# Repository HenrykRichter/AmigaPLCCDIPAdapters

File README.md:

# AmigaPLCCDIPAdapters
PLCC to DIP Adapters for Amiga Computers

The main part of this project are adapter PCB designs for Commodore PLCC chips to be used in conjunction
with DIP sockets in Amiga 500/2000/3000 computers. Since parts availability of those chips has dwindled in
recent years, the PLCC variants of CSG8373R4PL, CSG8364R7PL and CSG8520PL have become more interesting as
parts replacements.

Another sub-project in here is a replacement for the Video DAC (or Video Hybrid, CSG part number 390229-0x).
While other OpenSource designs exist for the Video Hybrid (e.g. from [Sukko Pera](https://github.com/SukkoPera/OpenAmigaVideoHybrid)), this
alternative design is based on 0603 parts and much smaller than other designs I am aware of. 
The Video Hybrid may be used in A500(+), A1000, A2000, A3000 and on Commodore's A2320 DeInterlacer. Like the
original, it supports 12 Bit RGB and monochrome composite outputs.

## Building Notes

I would suggest to solder the pin strips first. Once done, the best course of action is to shorten the
pins who sit under the PLCC socket. Mount the PLCC socket next and carefully solder its pins at the underside of the board.

## Parts list for Denise and Paula Adapters
- PCB
- 2 pin strips 2.54mm, 24 pins each (e.g. BKL 10120538 at Reichelt.de)
- 1 THT PLCC socket, 52 pins (e.g. 575-945224 at Mouser or PLCC 52 at Reichelt.de)

## Parts list for CIA Adapters
- PCB
- 2 pin strips 2.54mm, 20 pins each (e.g. BKL 10120536 at Reichelt.de)
- 1 THT PLCC socket, 44 pins (e.g. PLCC 44 at Reichelt.de)
- 1 pin strip angled 1x4 RM2.54 (e.g. W+P 946-134 at Reichelt.de), optional
Please note that the angled 1x4 connector is useful only if you are going to extract
the DTR or CTS signals for further use (CIA-B only). Otherwise, it doesn't need to
be fitted.

## Video Hybrid

The unfortunate side effect of a small board size is the lack of space for a nice silkscreen. Depending
on the available print resolution of the PCB manufacturer, the parts indicators might not be quite easily
visible. Consequently, I've put a picture into the Pics/ subfolder where the proper part locations are
identified.

## Pictures

## License
The PCB, it's design files and all support code are licensed as [CC BY NC SA](https://creativecommons.org/licenses/by-nc-sa/4.0/deed.en).

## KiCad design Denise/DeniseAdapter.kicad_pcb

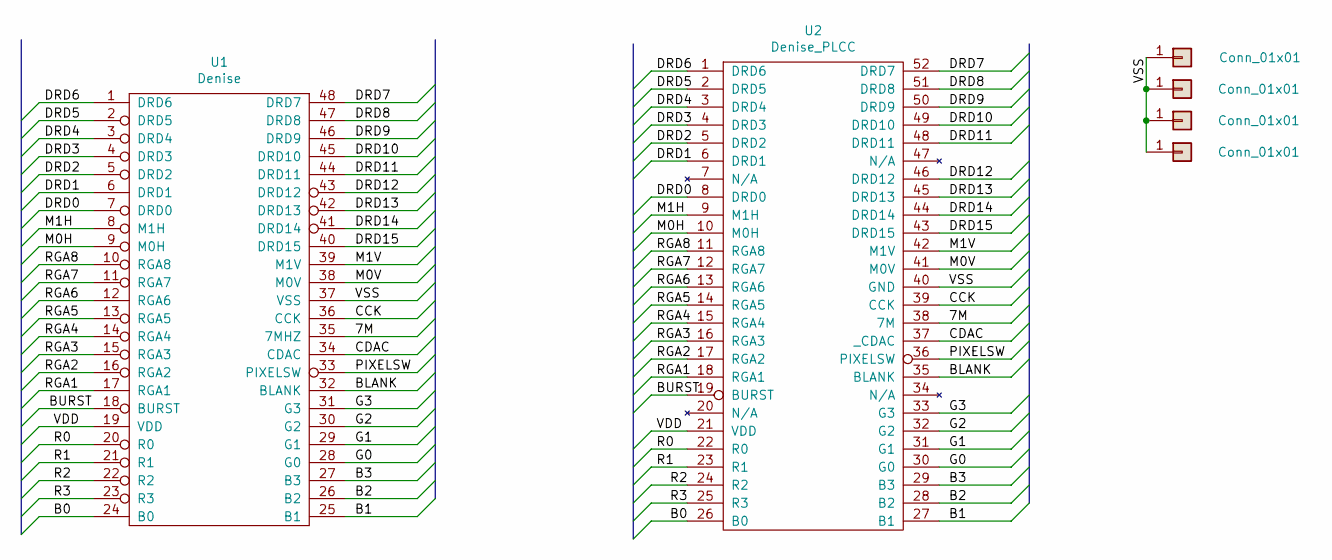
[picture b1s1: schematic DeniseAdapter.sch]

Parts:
J1, J2, J3, J4: Conn_01x01; MountingHole_3mm
U1: Denise; DIP-48_W15.24mm_Socket
U2: Denise_PLCC; PLCC-52_THT-Socket

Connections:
/7M: U1.35 (7MHZ), U2.38 (7M)
/B0: U1.24 (B0), U2.26 (B0)
/B1: U1.25 (B1), U2.27 (B1)
/B2: U1.26 (B2), U2.28 (B2)
/B3: U1.27 (B3), U2.29 (B3)
/BLANK: U1.32 (BLANK), U2.35 (BLANK)
/BURST: U1.18 (BURST), U2.19 (BURST)
/CCK: U1.36 (CCK), U2.39 (CCK)
/CDAC: U1.34 (CDAC), U2.37 (_CDAC)
/DRD0: U1.7 (DRD0), U2.8 (DRD0)
/DRD1: U1.6 (DRD1), U2.6 (DRD1)
/DRD2: U1.5 (DRD2), U2.5 (DRD2)
/DRD3: U1.4 (DRD3), U2.4 (DRD3)
/DRD4: U1.3 (DRD4), U2.3 (DRD4)
/DRD5: U1.2 (DRD5), U2.2 (DRD5)
/DRD6: U1.1 (DRD6), U2.1 (DRD6)
/DRD7: U1.48 (DRD7), U2.52 (DRD7)
/DRD8: U1.47 (DRD8), U2.51 (DRD8)
/DRD9: U1.46 (DRD9), U2.50 (DRD9)
/DRD10: U1.45 (DRD10), U2.49 (DRD10)
/DRD11: U1.44 (DRD11), U2.48 (DRD11)
/DRD12: U1.43 (DRD12), U2.46 (DRD12)
/DRD13: U1.42 (DRD13), U2.45 (DRD13)
/DRD14: U1.41 (DRD14), U2.44 (DRD14)
/DRD15: U1.40 (DRD15), U2.43 (DRD15)
/G0: U1.28 (G0), U2.30 (G0)
/G1: U1.29 (G1), U2.31 (G1)
/G2: U1.30 (G2), U2.32 (G2)
/G3: U1.31 (G3), U2.33 (G3)
/M0H: U1.9 (M0H), U2.10 (M0H)
/M0V: U1.38 (M0V), U2.41 (M0V)
/M1H: U1.8 (M1H), U2.9 (M1H)
/M1V: U1.39 (M1V), U2.42 (M1V)
/PIXELSW: U1.33 (PIXELSW), U2.36 (PIXELSW)
/R0: U1.20 (R0), U2.22 (R0)
/R1: U1.21 (R1), U2.23 (R1)
/R2: U1.22 (R2), U2.24 (R2)
/R3: U1.23 (R3), U2.25 (R3)
/RGA1: U1.17 (RGA1), U2.18 (RGA1)
/RGA2: U1.16 (RGA2), U2.17 (RGA2)
/RGA3: U1.15 (RGA3), U2.16 (RGA3)
/RGA4: U1.14 (RGA4), U2.15 (RGA4)
/RGA5: U1.13 (RGA5), U2.14 (RGA5)
/RGA6: U1.12 (RGA6), U2.13 (RGA6)
/RGA7: U1.11 (RGA7), U2.12 (RGA7)
/RGA8: U1.10 (RGA8), U2.11 (RGA8)
/VDD: U1.19 (VDD), U2.21 (VDD)
/VSS: J1.1, J2.1, J3.1, J4.1, U1.37 (VSS), U2.40 (GND)

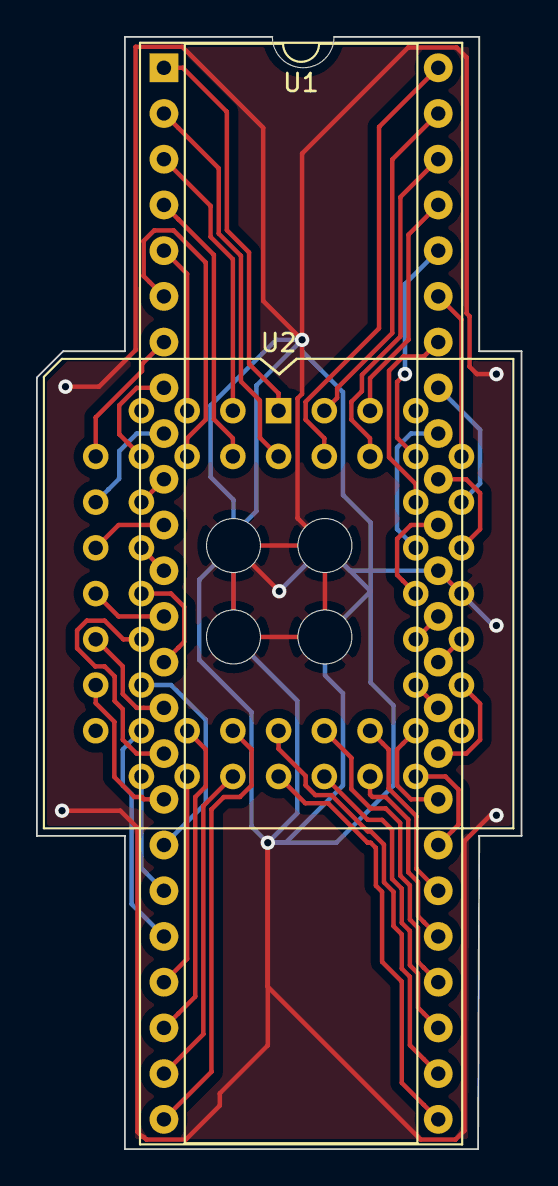
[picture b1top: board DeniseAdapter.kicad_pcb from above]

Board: 2 copper layers, 26.9 x 61.8 mm, 6 parts (0 on the bottom side), 48 nets.

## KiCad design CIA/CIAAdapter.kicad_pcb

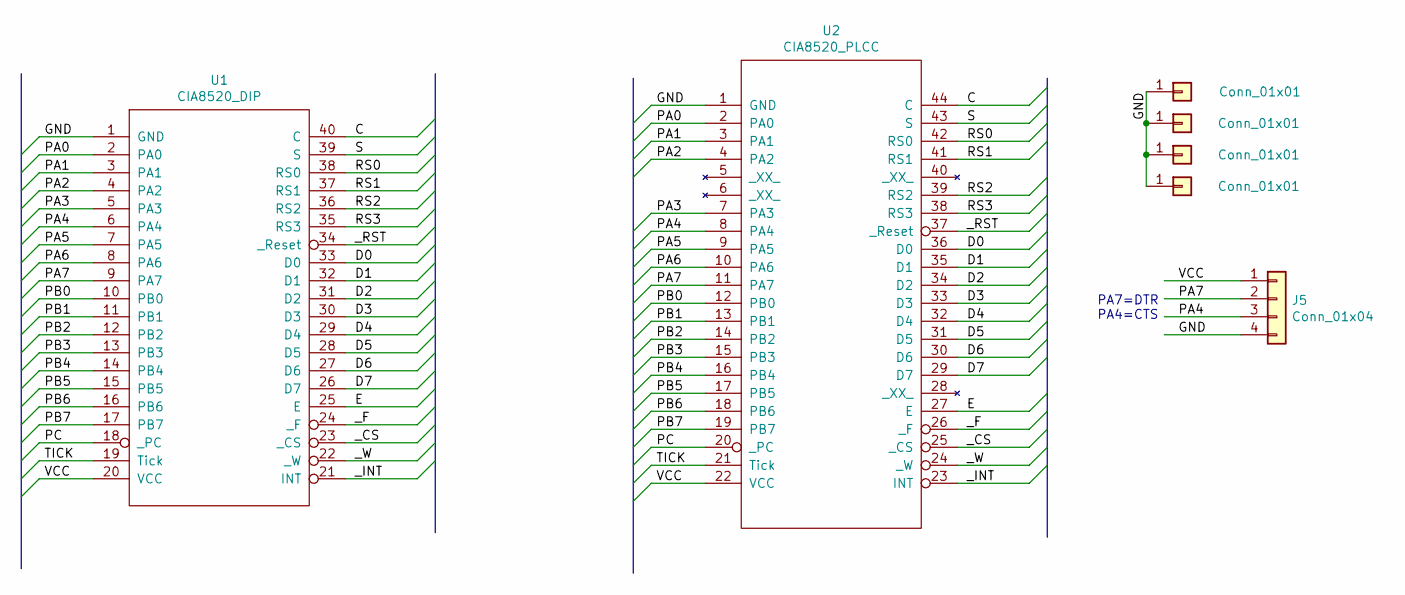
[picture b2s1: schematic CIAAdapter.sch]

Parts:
J1, J2, J3, J4: Conn_01x01; MountingHole_3mm
J5: Conn_01x04; PinHeader_1x04_P2.54mm_Vertical
U1: CIA8520_DIP; DIP-40_W15.24mm
U2: CIA8520_PLCC; PLCC-44_THT-Socket

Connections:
/C: U1.40 (C), U2.44 (C)
/D0: U1.33 (D0), U2.36 (D0)
/D1: U1.32 (D1), U2.35 (D1)
/D2: U1.31 (D2), U2.34 (D2)
/D3: U1.30 (D3), U2.33 (D3)
/D4: U1.29 (D4), U2.32 (D4)
/D5: U1.28 (D5), U2.31 (D5)
/D6: U1.27 (D6), U2.30 (D6)
/D7: U1.26 (D7), U2.29 (D7)
/E: U1.25 (E), U2.27 (E)
/GND: J1.1, J2.1, J3.1, J4.1, J5.4, U1.1 (GND), U2.1 (GND)
/PA0: U1.2 (PA0), U2.2 (PA0)
/PA1: U1.3 (PA1), U2.3 (PA1)
/PA2: U1.4 (PA2), U2.4 (PA2)
/PA3: U1.5 (PA3), U2.7 (PA3)
/PA4: J5.3, U1.6 (PA4), U2.8 (PA4)
/PA5: U1.7 (PA5), U2.9 (PA5)
/PA6: U1.8 (PA6), U2.10 (PA6)
/PA7: J5.2, U1.9 (PA7), U2.11 (PA7)
/PB0: U1.10 (PB0), U2.12 (PB0)
/PB1: U1.11 (PB1), U2.13 (PB1)
/PB2: U1.12 (PB2), U2.14 (PB2)
/PB3: U1.13 (PB3), U2.15 (PB3)
/PB4: U1.14 (PB4), U2.16 (PB4)
/PB5: U1.15 (PB5), U2.17 (PB5)
/PB6: U1.16 (PB6), U2.18 (PB6)
/PB7: U1.17 (PB7), U2.19 (PB7)
/PC: U1.18 (_PC), U2.20 (_PC)
/RS0: U1.38 (RS0), U2.42 (RS0)
/RS1: U1.37 (RS1), U2.41 (RS1)
/RS2: U1.36 (RS2), U2.39 (RS2)
/RS3: U1.35 (RS3), U2.38 (RS3)
/S: U1.39 (S), U2.43 (S)
/TICK: U1.19 (Tick), U2.21 (Tick)
/VCC: J5.1, U1.20 (VCC), U2.22 (VCC)
/_CS: U1.23 (_CS), U2.25 (_CS)
/_F: U1.24 (_F), U2.26 (_F)
/_INT: U1.21 (INT), U2.23 (INT)
/_RST: U1.34 (_Reset), U2.37 (_Reset)
/_W: U1.22 (_W), U2.24 (_W)

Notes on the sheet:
PA7=DTR PA4=CTS

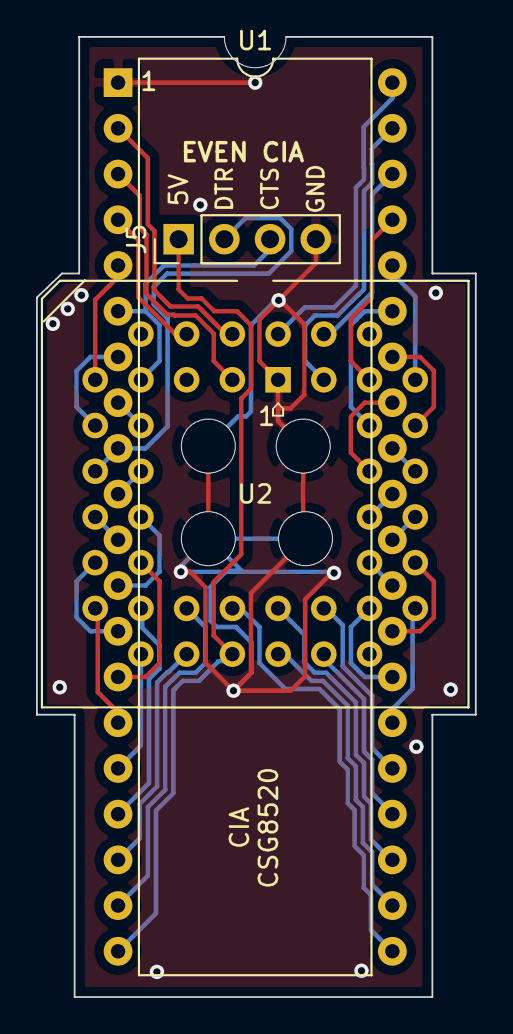
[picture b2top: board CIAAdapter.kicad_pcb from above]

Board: 2 copper layers, 24.4 x 53.3 mm, 7 parts (0 on the bottom side), 40 nets.

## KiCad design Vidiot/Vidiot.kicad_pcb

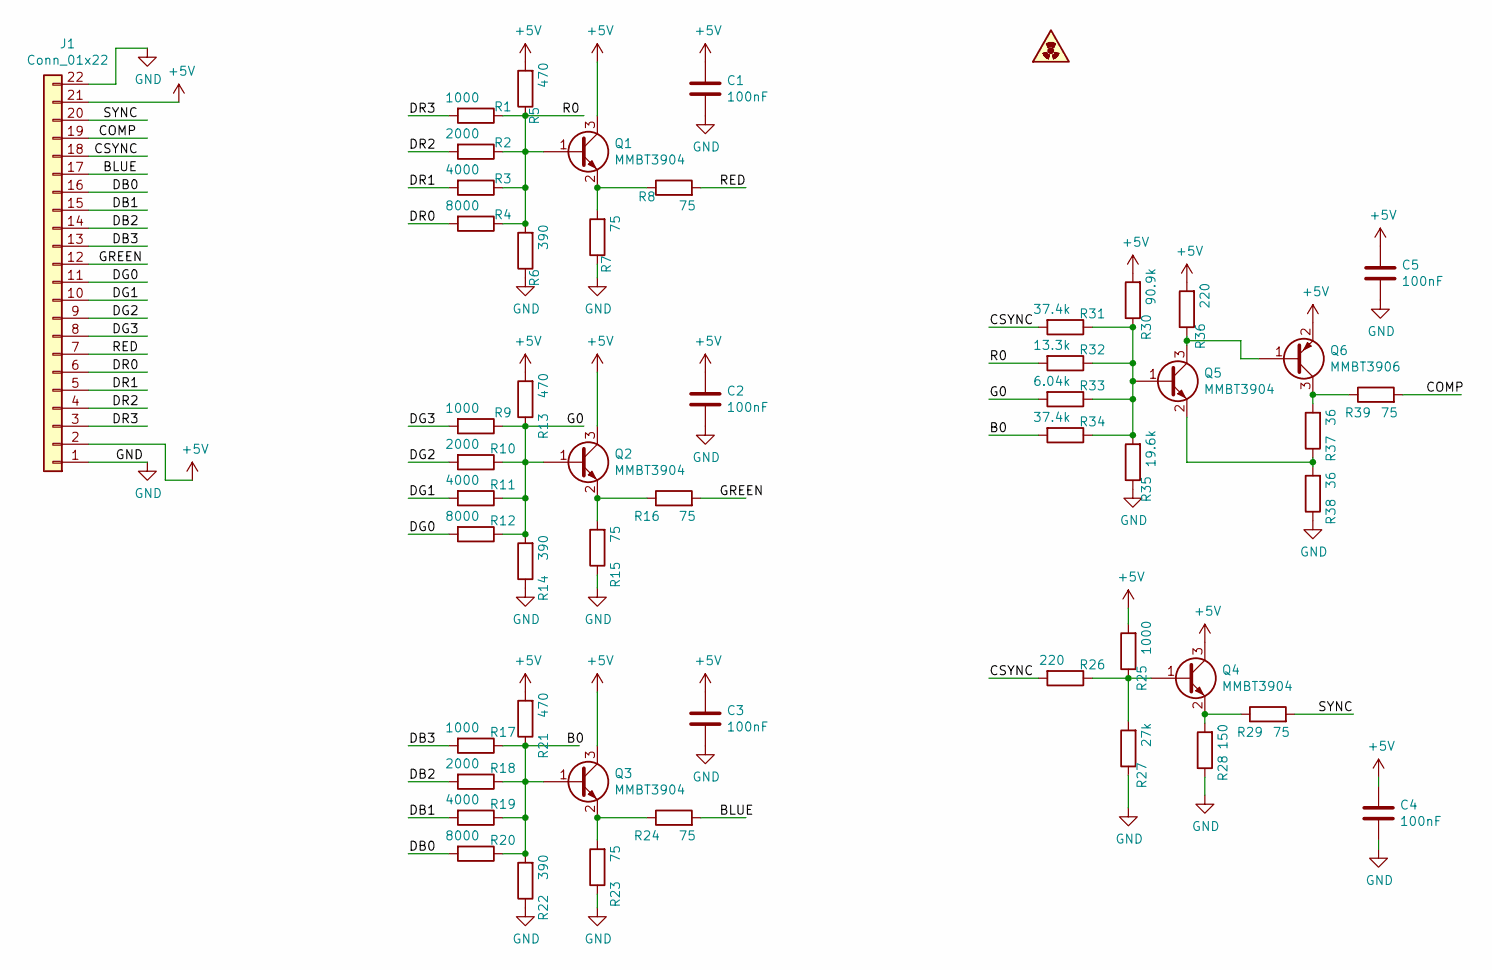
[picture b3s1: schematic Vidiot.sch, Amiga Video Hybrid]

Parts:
C1, C2, C3, C4, C5: 100nF; R_0603_1608Metric_Pad1.05x0.95mm_HandSolder
J1: Conn_01x22; PinHeader_1x22_P2.54mm_Horizontal
Q1, Q2, Q3, Q4, Q5: MMBT3904; SOT-23
Q6: MMBT3906; SOT-23
R1, R9, R17, R25: 1000; R_0603_1608Metric_Pad1.05x0.95mm_HandSolder
R2, R10, R18: 2000; R_0603_1608Metric_Pad1.05x0.95mm_HandSolder
R3, R11, R19: 4000; R_0603_1608Metric_Pad1.05x0.95mm_HandSolder
R4, R12, R20: 8000; R_0603_1608Metric_Pad1.05x0.95mm_HandSolder
R5, R13, R21: 470; R_0603_1608Metric_Pad1.05x0.95mm_HandSolder
R6, R14, R22: 390; R_0603_1608Metric_Pad1.05x0.95mm_HandSolder
R7, R8, R15, R16, R23, R24, R29, R39: 75; R_0603_1608Metric_Pad1.05x0.95mm_HandSolder
R26, R36: 220; R_0603_1608Metric_Pad1.05x0.95mm_HandSolder
R27: 27k; R_0603_1608Metric_Pad1.05x0.95mm_HandSolder
R28: 150; R_0603_1608Metric_Pad1.05x0.95mm_HandSolder
R30: 90.9k; R_0603_1608Metric_Pad1.05x0.95mm_HandSolder
R31, R34: 37.4k; R_0603_1608Metric_Pad1.05x0.95mm_HandSolder
R32: 13.3k; R_0603_1608Metric_Pad1.05x0.95mm_HandSolder
R33: 6.04k; R_0603_1608Metric_Pad1.05x0.95mm_HandSolder
R35: 19.6k; R_0603_1608Metric_Pad1.05x0.95mm_HandSolder
R37, R38: 36; R_0603_1608Metric_Pad1.05x0.95mm_HandSolder

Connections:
+5V: C1.1, C2.1, C3.1, C4.1, C5.1, J1.2, J1.21, Q1.3 (C), Q2.3 (C), Q3.3 (C), Q4.3 (C), Q6.2 (E), R5.2, R13.2, R21.2, R25.2, R30.2, R36.2
/B0: Q3.1 (B), R17.1, R18.1, R19.1, R20.1, R21.1, R22.2, R34.2
/BLUE: J1.17, R24.2
/COMP: J1.19, R39.2
/CSYNC: J1.18, R26.2, R31.2
/DB0: J1.16, R20.2
/DB1: J1.15, R19.2
/DB2: J1.14, R18.2
/DB3: J1.13, R17.2
/DG0: J1.11, R12.2
/DG1: J1.10, R11.2
/DG2: J1.9, R10.2
/DG3: J1.8, R9.2
/DR0: J1.6, R4.2
/DR1: J1.5, R3.2
/DR2: J1.4, R2.2
/DR3: J1.3, R1.2
/G0: Q2.1 (B), R9.1, R10.1, R11.1, R12.1, R13.1, R14.2, R33.2
/GREEN: J1.12, R16.2
/R0: Q1.1 (B), R1.1, R2.1, R3.1, R4.1, R5.1, R6.2, R32.2
/RED: J1.7, R8.2
/SYNC: J1.20, R29.2
GND: C1.2, C2.2, C3.2, C4.2, C5.2, J1.1, J1.22, R6.1, R7.1, R14.1, R15.1, R22.1, R23.1, R27.1, R28.1, R35.1, R38.1
unnamed: Q1.2 (E), R7.2, R8.1
unnamed: Q2.2 (E), R15.2, R16.1
unnamed: Q3.2 (E), R23.2, R24.1
unnamed: Q4.1 (B), R25.1, R26.1, R27.2
unnamed: Q4.2 (E), R28.2, R29.1
unnamed: Q5.1 (B), R30.1, R31.1, R32.1, R33.1, R34.1, R35.2
unnamed: Q5.2 (E), R37.1, R38.2
unnamed: Q5.3 (C), Q6.1 (B), R36.1
unnamed: Q6.3 (C), R37.2, R39.1

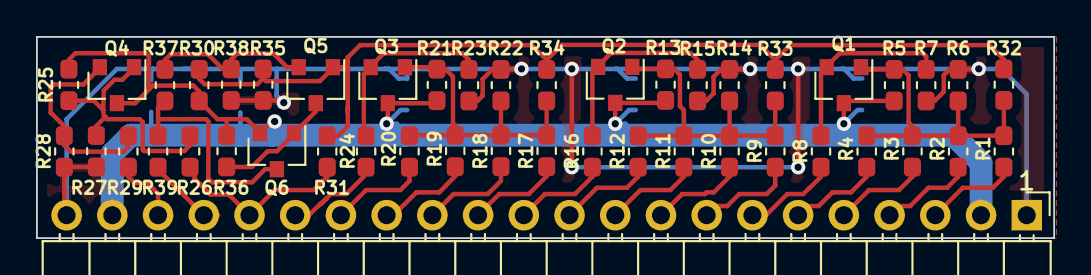
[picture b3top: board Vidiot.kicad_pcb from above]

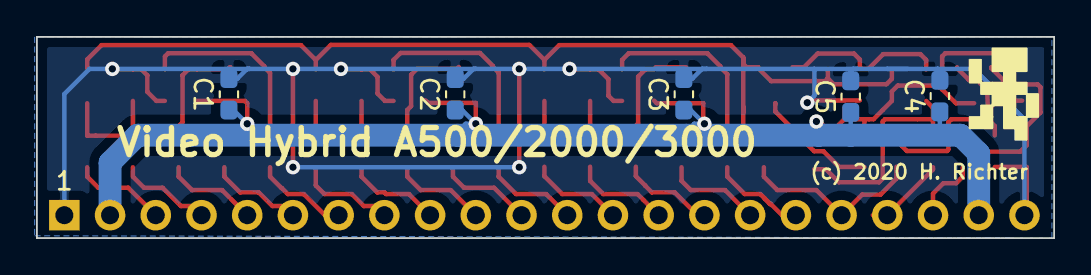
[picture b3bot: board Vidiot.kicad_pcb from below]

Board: 2 copper layers, 56.5 x 11.2 mm, 51 parts (5 on the bottom side), 32 nets.

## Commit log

2023-04-01 initial upload
2023-04-19 nicer board outline for Denise adapter

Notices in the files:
CIA/CIAAdapter.kicad_pcb:
© 2019-2023
Vidiot/Vidiot.kicad_pcb:
(c) 2020 H. Richter
